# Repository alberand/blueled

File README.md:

## Blueled - Bluetooth LED strip controller

This repo has hardware and firmware for Bluetooth LED strip controller based on
atmega328p (the same as in Arduino Nano).

Features:

* Android Application (not started yet)
* Custom colors and gradients
* ~15 different pre-set animation
* Over-The-Air Updates
* Python interface (to control it from PC)
* Save latest state between power on/off
* Up to 100 LEDs on full brightness (WS2812B)

#### Notes (to refactor)

Be careful with connection between programmer Arduino and target Arduino. I had
a lot of corrupted bytes during uploading bootloader/application with ISCP.

Add bluetooth:

    $ sudo systemctl start bluetooth
    $ sudo bluetoothctl
    $ power on
    $ scan on
    $ # You will see MAC of your HC-05
    $ trust <MAC>
    $ pair <MAC>
    $ # It will ask for pin
    $ # That's all!

Load rfcomm kernel module:

    sudo modprobe rfcomm 

Create serial port:

    sudo rfcomm bind rfcomm0 <MAC>

How to sniff bluetooth:
https://github.com/snarlistic/jpnevulator

    jpnevulator --tty=/dev/blueled --read --ascii

In case of problems with PC's bluetooth module try:

1. power on/off module through the bluetoothctl session
2. sudo rfkill unblock all

https://gist.github.com/0/c73e2557d875446b9603

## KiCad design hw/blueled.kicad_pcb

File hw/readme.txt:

Screw terminal:
https://www.gme.cz/svorkovnice-tl201v-03p-gs

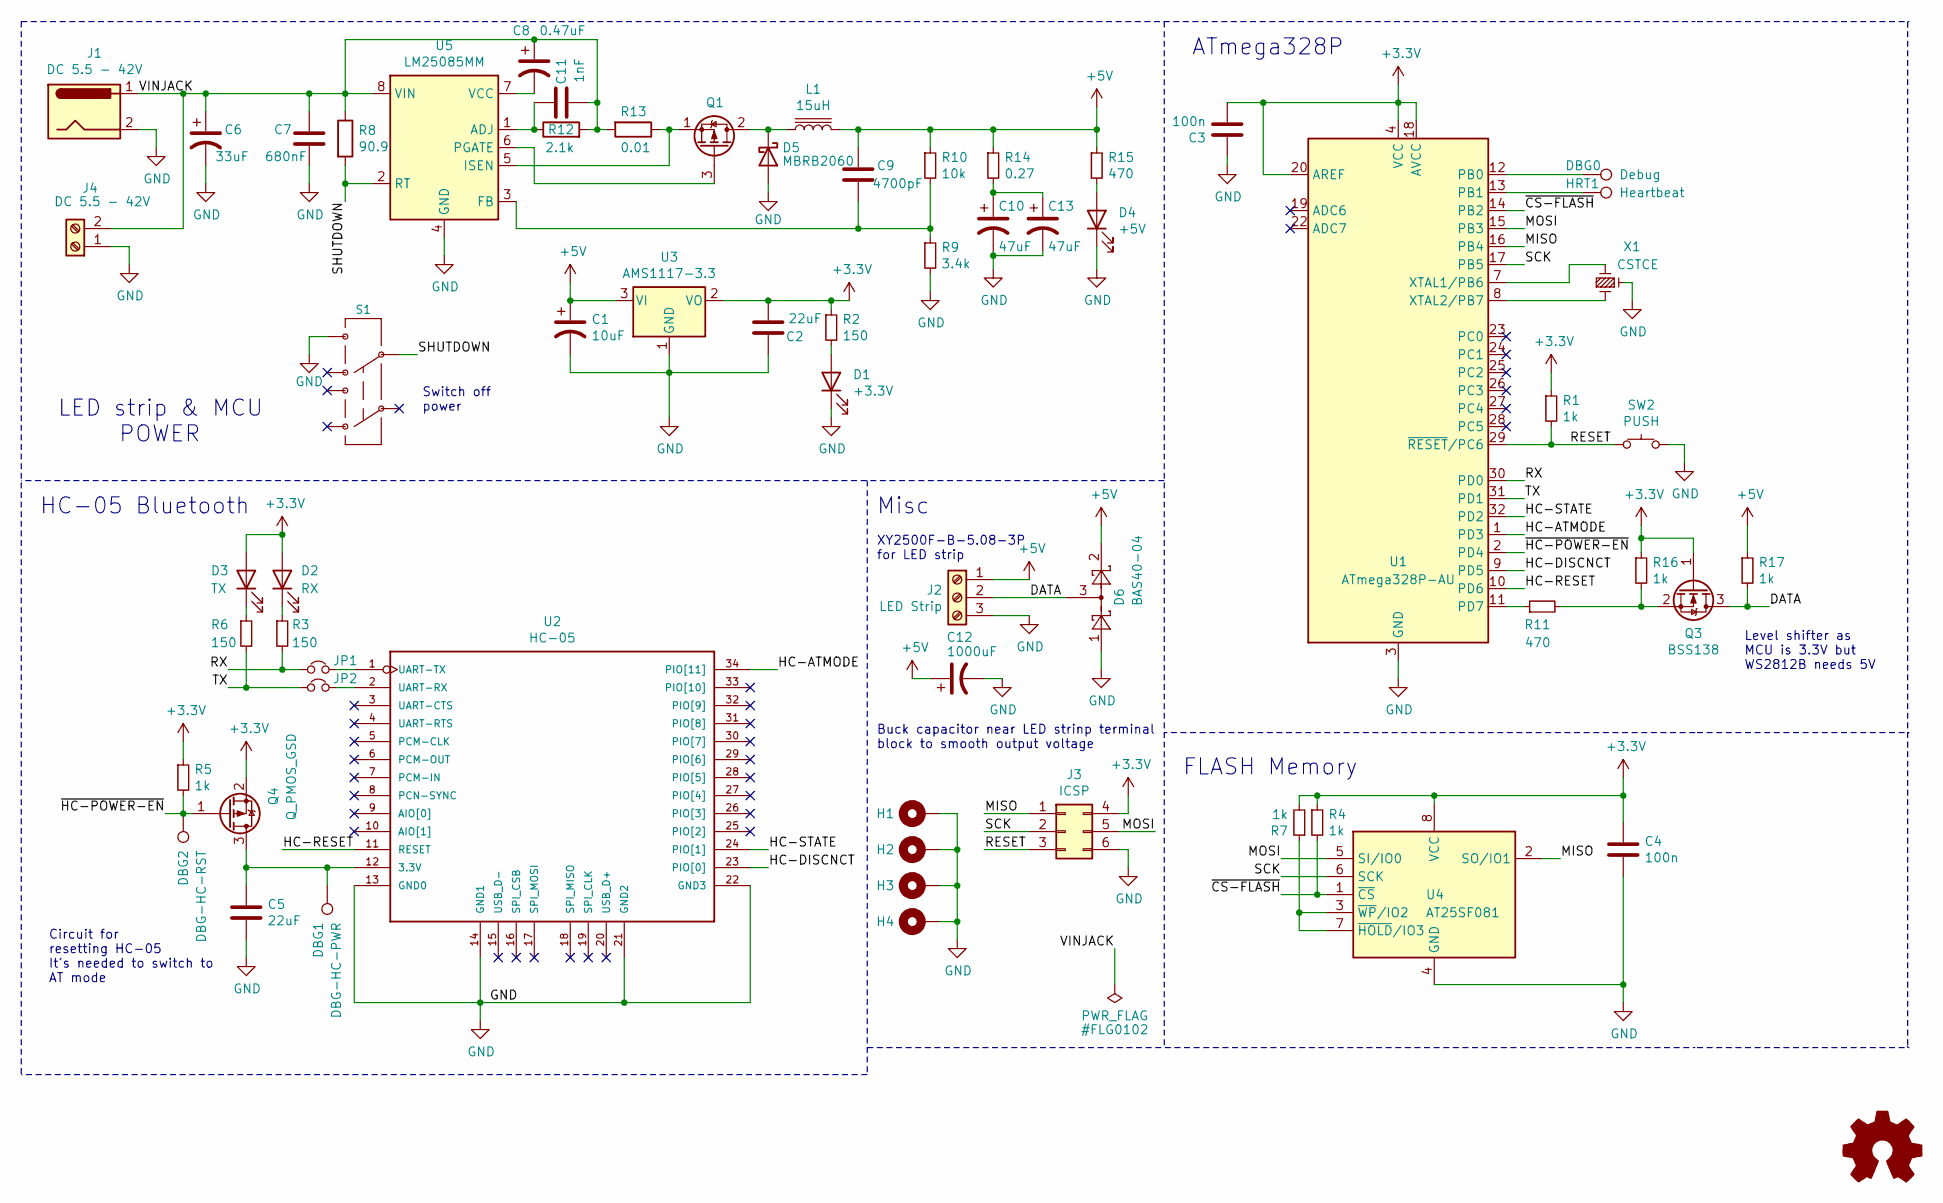
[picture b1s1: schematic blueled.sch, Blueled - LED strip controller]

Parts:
C1: 10uF; CP_EIA-3216-18_Kemet-A_Pad1.58x1.35mm_HandSolder; Manuf. Part TAJA106K016RNJ
C2, C5: 22uF; CP_EIA-3216-18_Kemet-A_Pad1.58x1.35mm_HandSolder; Manuf. Part 593D226X9004A2TE3
C3, C4: 100n; C_0805_2012Metric_Pad1.15x1.40mm_HandSolder; Manuf. Part CL21B104KBCNNNC
C6: 33uF; CP_Elec_10x10; Manuf. Part VZH330M2ATR-1010
C7: 680nF; C_0805_2012Metric_Pad1.15x1.40mm_HandSolder; Manuf. Part C2012X7S2A684KT000N
C8: 0.47uF; C_0805_2012Metric_Pad1.15x1.40mm_HandSolder; Manuf. Part C2012X7R1C474KT000N
C9: 4700pF; C_0805_2012Metric_Pad1.15x1.40mm_HandSolder; Manuf. Part C2012C0G1H472JT0H0N
C10, C13: 47uF; C_1210_3225Metric_Pad1.42x2.65mm_HandSolder; Manuf. Part C3225X5R0J476MT000N
C11: 1nF; C_0805_2012Metric_Pad1.15x1.40mm_HandSolder; Manuf. Part C2012X7R2A102KT020S
C12: 1000uF; CP_Elec_10x10; Manuf. Part VEU102M0JTR-1010
D1: +3.3V; LED_0805_2012Metric_Pad1.15x1.40mm_HandSolder; Manuf. Part TJ-S1608SW6TGLC2G-A5
D2: RX; LED_0805_2012Metric_Pad1.15x1.40mm_HandSolder; Manuf. Part TJ-S1608SW6TGLC2R-A5
D3: TX; LED_0805_2012Metric_Pad1.15x1.40mm_HandSolder; Manuf. Part TJ-S1608SW6TGLC2R-A5
D4: +5V; LED_0805_2012Metric_Pad1.15x1.40mm_HandSolder; Manuf. Part TJ-S1608SW6TGLC2G-A5
D5: MBRB2060; TO-263-3_TabPin2; Manuf. Part MBRB2060CT
D6: BAS40-04; SOT-23; Manuf. Part BAS40-04
DBG0: Debug; TestPoint_Pad_D1.0mm
DBG1: DBG-HC-PWR; TestPoint_Pad_D1.0mm
DBG2: DBG-HC-RST; TestPoint_Pad_D1.0mm
H1, H2, H3, H4: MountingHole_Pad; MountingHole_3.2mm_M3
HRT1: Heartbeat; TestPoint_Pad_D1.0mm
J1: DC 5.5 - 42V; BarrelJack_Horizontal; Manuf. Part DC-005-5A-2.0
J2: LED Strip; TerminalBlock_bornier-3_P5.08mm; Manuf. Part XY2500R-D-5.08-3P
J3: ICSP; PinHeader_2x03_P2.54mm_Vertical
J4: DC 5.5 - 42V; TerminalBlock_bornier-2_P5.08mm; Manuf. Part WJ15EDGRC-3.81-2P
JP1, JP2: Jumper_NC_Small; SolderJumper-2_P1.3mm_Bridged_Pad1.0x1.5mm
L1: 15uH; SMMS1350-150M; Manuf. Part MWSA1004S-150MT
Q1: Q_PMOS_SDG; TO-252-3_TabPin4; Manuf. Part AOD4185L
Q3: BSS138; SOT-23; Manuf. Part BSS138
Q4: Q_PMOS_GSD; SOT-23; Manuf. Part IRLML6402
R1, R4, R5, R7, R16, R17: 1k; R_0805_2012Metric_Pad1.15x1.40mm_HandSolder; Manuf. Part RC0805FR-071KL
R2, R3, R6: 150; R_0805_2012Metric_Pad1.15x1.40mm_HandSolder; Manuf. Part RC0805FR-07150RL
R8: 90.9; R_0805_2012Metric_Pad1.15x1.40mm_HandSolder; Manuf. Part RK73B2ATTD102J
R9: 3.4k; R_0805_2012Metric_Pad1.15x1.40mm_HandSolder; Manuf. Part RC0805FR-073K4L
R10: 10k; R_0805_2012Metric_Pad1.15x1.40mm_HandSolder; Manuf. Part RC0805FR-0710KL
R11, R15: 470; R_0805_2012Metric_Pad1.15x1.40mm_HandSolder; Manuf. Part RC0805FR-07470RL
R12: 2.1k; R_0805_2012Metric_Pad1.15x1.40mm_HandSolder; Manuf. Part RC0805FR-072K1L
R13: 0.01; R_2512_6332Metric_Pad1.52x3.35mm_HandSolder; Manuf. Part RL2512JK-070R01L
R14: 0.27; R_0805_2012Metric_Pad1.15x1.40mm_HandSolder; Manuf. Part RL0805JR-070R27L
S1: SWITCH-DPDT-PTH-GPI-152-3013; XKB7070-Z; Manuf. Part XKB7070-Z
SW2: PUSH; SW_SPST_FSMSM; Manuf. Part K2-1107ST-A4SW-06
U1: ATmega328P-AU; TQFP-32_7x7mm_P0.8mm; Manuf. Part ATmega328P-AU
U2: HC-05; BT34P-SMD-1.5-26.9X13.0X2.2MM
U3: AMS1117-3.3; SOT-223; Manuf. Part AMS1117-3.3
U4: AT25SF081; SOIC-8_3.9x4.9mm_P1.27mm; Manuf. Part AT25SF081-SHD-T
U5: LM25085MM; VSSOP-8_3.0x3.0mm_P0.65mm; Manuf. Part LM25085MM/NOPB
X1: CSTCE; Resonator_SMD_muRata_CSTNE_3Pin_3.2x1.3mm; Manuf. Part CSTNE8M00G55Z000R0

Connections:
+3V3: C2.2, C3.2, C4.1, D2.2 (A), D3.2 (A), J3.4, Q3.1 (G), Q4.2 (S), R1.1, R2.1, R4.1, R5.1, R7.2, R16.1, U1.4 (VCC), U1.6 (VCC), U1.18 (AVCC), U1.20 (AREF), U3.2 (VO), U4.8 (VCC); also elsewhere on the board
+5V: C1.1, C9.1, C12.1, D6.2, J2.1, L1.2, R10.1, R14.1, R15.1, R17.1, U3.3 (VI)
/DATA: D6.3, J2.2, Q3.3 (D), R17.2
/HC-ATMODE: U1.1 (PD3), U2.34 (PIO[11])
/HC-DISCNCT: U1.9 (PD5), U2.23 (PIO[0])
/HC-RESET: U1.10 (PD6), U2.11 (RESET)
/HC-STATE: U1.32 (PD2), U2.24 (PIO[1])
/MISO: J3.1, U1.16 (PB4), U4.2 (SO/IO1)
/MOSI: J3.5, U1.15 (PB3), U4.5 (SI/IO0)
/RESET: J3.3, R1.2, SW2.1, U1.29 (~RESET~/PC6)
/RX: JP1.1, R3.2, U1.30 (PD0)
/SCK: J3.2, U1.17 (PB5), U4.6 (SCK)
/SHUTDOWN: R8.2, S1.5, U5.2 (RT)
/TX: JP2.1, R6.2, U1.31 (PD1)
/VINJACK: C6.1, C7.1, C8.1, C11.1, J1.1, J4.2, R8.1, R12.2, R13.2, U5.8 (VIN); also elsewhere on the board
/~CS-FLASH: R4.2, U1.14 (PB2), U4.1 (~CS)
/~HC-POWER-EN: DBG2.1, Q4.1 (G), R5.2, U1.2 (PD4)
GND: C1.2, C2.1, C3.1, C4.2, C5.2, C6.2, C7.2, C10.2, C12.2, C13.2, D1.1 (K), D4.1 (K), D5.2 (A), D6.1, H1.1, H2.1, H3.1, H4.1, J1.2, J2.3, J3.6, J4.1, R9.2, S1.6, SW2.2, U1.3 (GND), U1.5 (GND), U1.21 (GND), U2.13 (GND0), U2.14 (GND1), U2.21 (GND2), U2.22 (GND3), U3.1 (GND), U4.4 (GND), U5.4 (GND), X1.2; also elsewhere on the board
unnamed: C5.1, DBG1.1, Q4.3 (D), U2.12 (3.3V)
unnamed: C8.2, U5.7 (VCC)
unnamed: C9.2, R9.1, R10.2, U5.3 (FB)
unnamed: C10.1, C13.1, R14.2
unnamed: C11.2, R12.1, U5.1 (ADJ)
unnamed 23: D1.2 (A), R2.2; also elsewhere on the board
unnamed 24: D2.1 (K), R3.1; also elsewhere on the board
unnamed 25: D3.1 (K), R6.1; also elsewhere on the board
unnamed 26: D4.2 (A), R15.2; also elsewhere on the board
unnamed: D5.1 (K), L1.1, Q1.2 (D)
unnamed: DBG0.1, U1.12 (PB0)
unnamed: HRT1.1, U1.13 (PB1)
unnamed: JP1.2, U2.1 (UART-TX)
unnamed: JP2.2, U2.2 (UART-RX)
unnamed: Q1.1 (S), R13.1, U5.5 (ISEN)
unnamed: Q1.3 (G), U5.6 (PGATE)
unnamed: Q3.2 (S), R11.2, R16.2
unnamed: R7.1, U4.3 (~WP~/IO2), U4.7 (~HOLD~/IO3)
unnamed: R11.1, U1.11 (PD7)
unnamed: U1.7 (XTAL1/PB6), X1.3
unnamed: U1.8 (XTAL2/PB7), X1.1

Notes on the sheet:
Misc
HC-05 Bluetooth
LED strip & MCU POWER
Buck capacitor near LED strinp terminal block to smooth output voltage
Circuit for resetting HC-05 It's needed to switch to AT mode
XY2500F-B-5.08-3P for LED strip
Switch off power
FLASH Memory
ATmega328P
Level shifter as MCU is 3.3V but WS2812B needs 5V

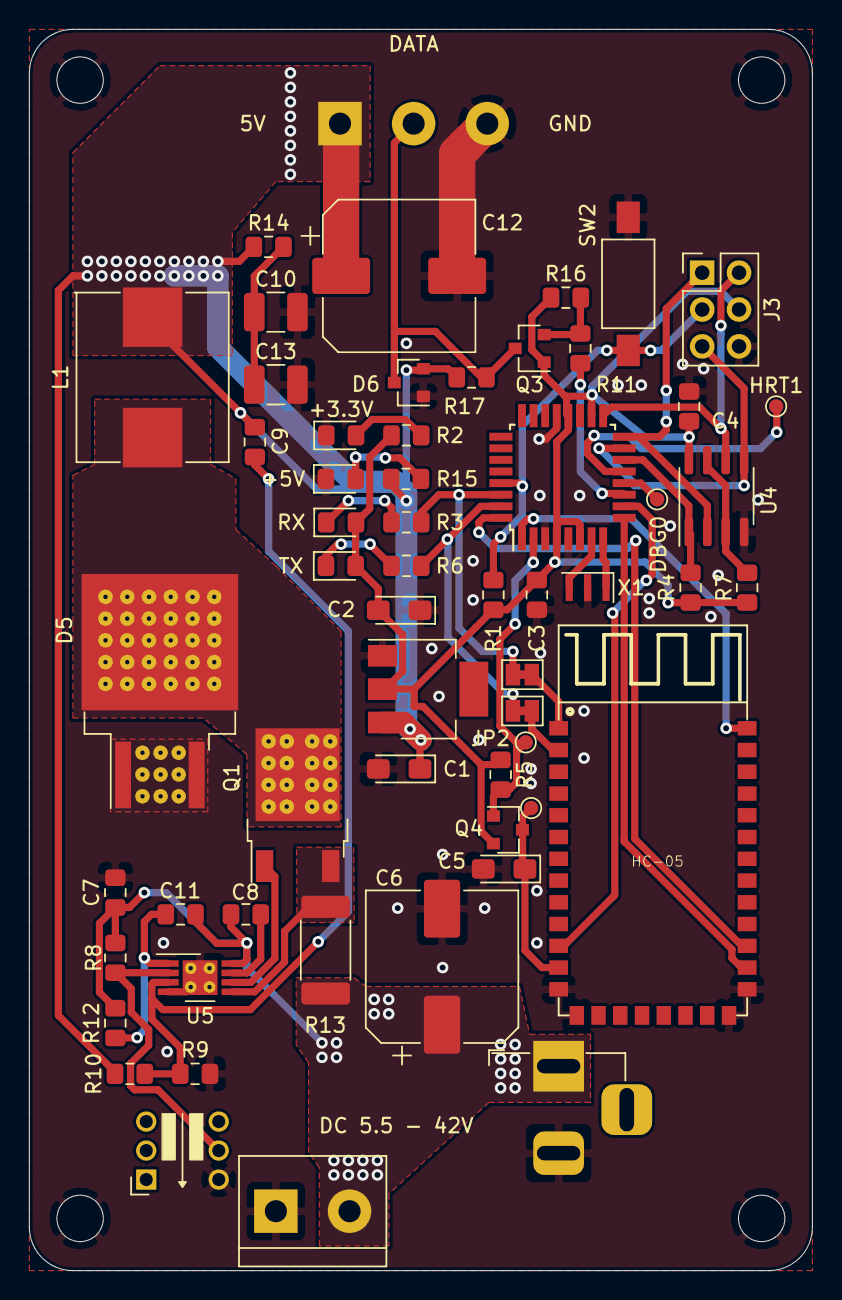
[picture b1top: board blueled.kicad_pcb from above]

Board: 2 copper layers, 54.0 x 85.6 mm, 62 parts (0 on the bottom side), 39 nets.

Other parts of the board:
+3.3V: +3.3V; LED_0805_2012Metric_Pad1.15x1.40mm_HandSolder
+5V: +5V; LED_0805_2012Metric_Pad1.15x1.40mm_HandSolder
DC 5.5 - 42V: DC 5.5 - 42V; BarrelJack_Horizontal
RX: RX; LED_0805_2012Metric_Pad1.15x1.40mm_HandSolder
TX: TX; LED_0805_2012Metric_Pad1.15x1.40mm_HandSolder

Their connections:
+3V3: RX.2, TX.2; also elsewhere on the board
/VINJACK: DC 5.5 - 42V.1; also elsewhere on the board
GND: +3.3V.1, +5V.1, DC 5.5 - 42V.2; also elsewhere on the board
unnamed 23: +3.3V.2; also elsewhere on the board
unnamed 24: RX.1; also elsewhere on the board
unnamed 25: TX.1; also elsewhere on the board
unnamed 26: +5V.2; also elsewhere on the board

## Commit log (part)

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2019-02-12 Remove tags file
2019-05-14 Add hardware part
    Board is drawn. I decided to not to install reset button and use test point between reset pin and ground
2019-05-14 Add initial version of parser
2019-06-13 Add optiboot submodule
2019-06-13 hw: Get rid of "ambient" name -> now "blueled"
2019-06-13 hw: Remove components.csv
2019-06-17 Add experiments folder + Add experiment of combining app and bootloader
    The combined HEX can be uploaded via ISCP interface
2019-06-17 Add README with some notes
2019-06-17 Add ISCP port to schematics
2019-06-17 Add patch to make optiboot wait longer
2019-07-28 docs: Add first issue and template
    I think it is useful to track, describe and explain issues which I face
    during the development. Issues on the gitlab/github are useful but they
    are suited for implementation problems/bugs. These issues more like
    design/architecture-ish
2019-07-28 docs: Update template to new format
    The issues appears and evolve with time. So, why to
    restrict and force people to describe the problems with non-native
    format. I think timeline is much more useful. Github/lab issuies
    are already as timeline
2019-07-28 hw: Mainly refactoring + add switch to the schematics
2019-07-29 Rename relay issui and add new results of research
2019-08-07 Add KiCAD's files
2019-08-07 docs: Add SPI EEPROM chip's datasheet
2019-08-07 Remove backup and autosave files
2019-08-07 Remove some file-formats from gitignore (KiCAD's)
2019-08-07 New version of hardware
    * SPI chip is added but not routed
    * Power switch MOSFET is added
    * Power flags added
    * SPI pins are moved to the right
2019-08-10 Add source link for the P-MOSFET reverse polarity protection
2019-08-10 Make pads for SMD components bigger and general rerouting
2019-08-18 HW: Remove big pads for MOSFET
2019-08-18 Add README for docs with collection intresting information
2019-08-25 docs: Another useful Manual for HC-05
2019-08-25 docs: Bluetooth address decoding
2019-08-25 docs: Useful Bluetooth classes/codes defenitions
2019-08-25 docs: Add instruction on how to get into AT mode
2019-08-25 Add region for VIN
2019-08-25 Minor updates
2019-09-01 Rev 0.1
2019-09-01 Add gerber files sent to manufacture
2019-09-24 Add PIO folder to gitignore
2019-09-24 sw: Remove old sources
2019-10-12 fix(docs): change status of #1 issue to complete
2019-10-12 add(docs): add #2 issue about layout of data line
2019-10-12 fix(env): clean up platformio config
2019-10-12 add(test): add template and example for future unit tests
2019-10-15 add(lib): add fifo
2019-10-15 fix(lib): implement fifo
2019-10-15 fix(fifo): remove src folder
2019-10-22 add: environment for native tests
2019-10-22 test: add fifo tests
2019-10-22 add: src folder with blink sample
2019-12-07 add(hw): moving to new layout
2019-12-07 fix(test): delete object otherwise stack overflows
2019-12-30 docs: Add atmega328p datasheet
2019-12-30 add: Makefile to combined HEX experiment
    It is used to combine firmware and bootloader into one
    HEX file and upload it into arduino
2019-12-30 add(pio): Add targets for vanilla arduino and uploading through ISP
2019-12-31 add: TinyFrame submodule
2020-03-27 refactor: remove TinyFrame
2020-03-27 fix: minor change in configuration of pio
2020-03-27 add: first working version of firmware
2020-03-27 doc: minor notes in README
2020-03-29 add: more animations
2020-03-31 add: udev rule
2020-03-31 fix: move static structs to cpp as they are used there
2020-03-31 fix: use FastLED 3.3.2 as 3.3.3 seem to fail to compile
2020-04-01 doc: add features to the readme
2020-04-01 add: patch for the newest optiboot
2020-04-01 add: build dir to gitignore
2020-04-01 Update optiboot submodule
2020-04-01 add: Makefile to create bootloader + application hex
2020-04-01 add: start update of hw to new rev
2020-04-12 add: datasheets for all components
2020-04-12 add: footprint for XKB7070-Z/X
2020-04-12 add: footprint for Murata SMD resonator
2020-04-12 refactor: remove unused
2020-04-12 add: schematics update
2020-04-19 add: finish layouting
2020-04-19 fix: readme as markdown
2020-04-23 add: tantalum capacitor to the linear regulator
2020-04-23 add: datasheet for tantalum capacitor
2020-04-23 fix: uncomment avrdude in makefile
2020-04-23 add: missing 3d models
2020-04-23 add: missing Barrel Jack model
2020-04-24 fix: colorize 3D models
2020-04-24 fix: move tantalum capacitor from switch
2020-04-24 add: image of rendered 3D model
2020-04-25 fix: MOSFET pin mapping and better layouting
2020-04-27 add: new effects
2020-04-27 refactor: get rid of switch cases for readability and easier addition of new animations
    I googled and seems like on small sets switch-case is the same in speed as for loop
    So, not a big deal but I want to try it this way
2020-04-27 refactor: missing spaces in PIO config
2020-04-27 refactor: remove unused config.hpp
2020-04-27 add: simple crude demo of SIMPAP
2020-04-29 fix: +3.3 net + page description and date
2020-04-29 add: jumpers to pcb layout
2020-04-29 refactor: some minor list formatting
2020-04-29 add: template for "train" animation
2020-04-29 fix: boot imediatly if PD2 is low wait 8s otherwise
    Seems like WATCHDOG_OFF doesn't do what I expected =)
2020-04-29 add: compile application before uploading
2020-04-29 fix: remove patch before applying it on Optiboot
2020-04-29 fix: path to *.hex and baudrate
2020-05-02 fix: data conversion in macro
2020-05-02 add(simpap): crude implementation in Python
2020-05-05 add: implementation of train effect
2020-06-01 add: simpap_protocol.py for ipy
2020-06-01 add: hw snapshot
2020-06-01 add: customizable LED strip size
2020-06-01 add: move astyle to pre-commit
2020-06-01 refactor: apply astyle to sources
2020-06-01 fix: improve pre-commit
2020-06-01 add: cppcheck to makefile
2020-06-02 add: simpap package initialization for IPY
2020-06-02 add: example of ipy simpap session
2020-06-02 fix: use interceptty as Bluetooth sniffer
    jpnevulator appear to be unable to behave as passtrhough
2020-06-02 add: atexit callback for simpap
2020-06-07 add: macros to find out position in the period
2020-06-07 add: color_wipe animation
2020-06-07 add: functions for command execution in ipy
2020-06-07 fix: experimenting with pre-commit
2020-06-30 refactor: hugh refactoring
2020-06-30 add(simpap): increase message size
2020-06-30 fix: remove debug code
2020-07-06 add: saving application state to EEPROM
2020-07-06 refactor(simpap): minor refactoring of python interface
2020-07-17 fix: minor animation changes
2020-07-19 add: pin for debugging
2020-07-26 fix: handle simpap_accept_char return code
2020-09-13 fix: don't use malloc
2020-09-13 refactor: minor changes to simpap
2020-09-13 add: simulation target
2020-09-13 fix: pre-commit hook don't add staged files
2020-09-13 fix: train() animation
2020-09-19 add(animation): classic rainbow & theater chase
2020-09-19 fix: save state after it's reset
2020-10-01 fix: many minor fixes
2020-10-01 fix: slow down serial + add fire animation
2020-10-01 fix: increase msg size + minor fixes
2020-10-01 add: new protocol structure
2020-10-03 add: compilation artifacts to gitignore
2020-10-03 fix: monitor speed
2020-10-04 fix: finally stable communication
2020-10-10 refactor: minor refactor
2020-10-14 test: experiments with fire animation
2020-10-14 refactor: major refactoring
2020-10-25 fix: working animation parametrization
2020-10-28 fix: handle exceptions
2020-10-28 fix: size in animation config in uint32_t not in bytes and config saving
2020-10-28 fix: gracefully exit on CTRL-D in ipy
2020-10-28 fix: gradient with 2 colors
2020-10-28 docs: update readme
2020-10-28 fix: don't accept commands if not in communication
2020-10-30 fix: many minor fixes with communication
2020-10-31 refactor: number are received in little-endian
2020-10-31 refactor: hugh refactoring of communication lib
2020-10-31 add: examples dir
2020-10-31 fix: memory leak
2020-10-31 add: rainbow example
2020-10-31 refactor: test example
2020-11-01 add: brightness command
2020-11-01 add: set_leds/brightness command to python interface
2020-11-01 fix: use CPP casting
2020-11-01 fix: last config ID constant
2020-11-02 fix: ws2812b have GRB instead of RGB
2020-11-02 fix: these are actually uint32_t
    But most of them have much smaller range
2020-11-04 refactor: cleaning of schematics
2020-11-07 add: heartbeat pin
2020-11-07 add: DC-to-DC converter + redone schematics
2020-11-07 fix(hw): more minor fixes
2020-11-09 fix: maximaze number of colors for gradient
2020-11-09 add: set color ranges
2020-11-19 fix: minor adjustments of the schematics
2020-11-21 add(hw): value to resistor
2020-11-22 add: integration with ledfx
2020-11-22 fix: update python interface to new message format
2020-11-23 add: state saving and loading
2020-11-23 fix: set_leds() didn't work
2020-11-24 add: speed up communication (115200 baudrate)
2020-11-24 fix: set number of received parameters to animation state
2020-11-25 add: segments() to python interface
2020-11-26 add(hw): updating BOM
2020-11-26 fix: heartbeat pin wasn't working
2020-11-26 add(hw): resistor for ENA of DC/DC
2020-11-27 add: common message header
2020-11-27 fix: wrong variable name
2020-11-28 add: notebook with script for screen capture
2020-11-28 fix(simpap): wrong reference + remove argument in segments()
2020-11-28 add: first draft of the extend-screen.py
2020-11-29 add: demo of timer
2020-11-30 add: stable communication and update?
2020-12-01 fix: increase rate up to 28 Hz (35 ms)
    Also did some test how stable it works. Looks good
2020-12-05 add: script for simulation of ambient light
2020-12-05 fix: automatically calculate number of parameters
2020-12-05 add: enable correct brown-out-detection level on the board
2020-12-05 fix: EN should be floating
2020-12-05 add: power supply is based on LM25085
2020-12-05 add: missing comments (more to go)
2020-12-05 add: better terminal block for led connection
2020-12-05 add: watchdog resetting
2020-12-05 fix(hw): more changes to power supply scheme
2020-12-07 fix(hw): fix rules checker issues
2020-12-07 add(hw): new netlist
2020-12-07 add(hw): BOM updates
2020-12-09 add(hw): more components in BOM
2020-12-10 add(hw): more BOM updates
2020-12-10 add: simple demo of weather script
2020-12-12 add: picker script
2020-12-13 add(hw): more footprints and boms
2020-12-19 add(hw): some capacitors to BOM
2020-12-20 add(hw): almost done with assigning capacitors
2020-12-21 add(hw): update resistors in BOM
2020-12-26 add(hw): component assignment is done
2020-12-26 refactor(hw): minor fixes
2020-12-26 add(hw): board sizes according to ISO/IEC 7810 ID-1
2020-12-26 refactor(hw): removing old traces and rearrangments
2020-12-28 add(hw): footprints for terminal blocks
2020-12-28 fix(hw): replace VIN with +5V
2020-12-28 add(hw): initial layout for v2.0
2020-12-29 add(hw): minor adjacements of output filter
2020-12-29 add(hw): a lot of progress in layouting + bug fixes
2020-12-30 add(hw): level shifter + layout progress
2020-12-30 add(hw): routed level shifter
2020-12-30 add(hw): almost finished layout
2021-01-01 add(hw): thermal vias and vias on high current traces
    https://www.eevblog.com/forum/projects/via-stitching-for-high-current-traces/
2021-01-01 fix(hw): change input cap + minor fixes
2021-01-01 fix(hw): minor adjustments (shorter current loop)
2021-01-02 add(hw): labels and 3D models
2021-01-02 add(hw): 3D export of PCB
2021-01-02 add(doc): 3D render of the board
2021-01-12 add: new BOM and update *.sch to new symbol lib
2021-01-14 refactor(pio): reorganize pio.ini + add WS2812FX
2021-01-14 add: integration with WS2812B
2021-01-14 fix: correct triggering of show()
2021-01-14 add: NeoPixel lib to deps
2021-01-31 refactor: change page settings
2021-01-31 add: MOSFET for HC-05 power switch
2021-01-31 Revert "add: integration with WS2812B"
    This reverts commit f4b76e52d401eaebef58efb1243d73c20fc64a66.
2021-01-31 Revert "add: NeoPixel lib to deps"
    This reverts commit a6f24fb2e979e7786ad81e0e419721aff0698d1c.
2021-01-31 fix: revert changes from other branch
2021-01-31 fix: update silkscreen labels
2021-01-31 add: new gerbers
2021-09-01 fix: set CPU freq in project settings
